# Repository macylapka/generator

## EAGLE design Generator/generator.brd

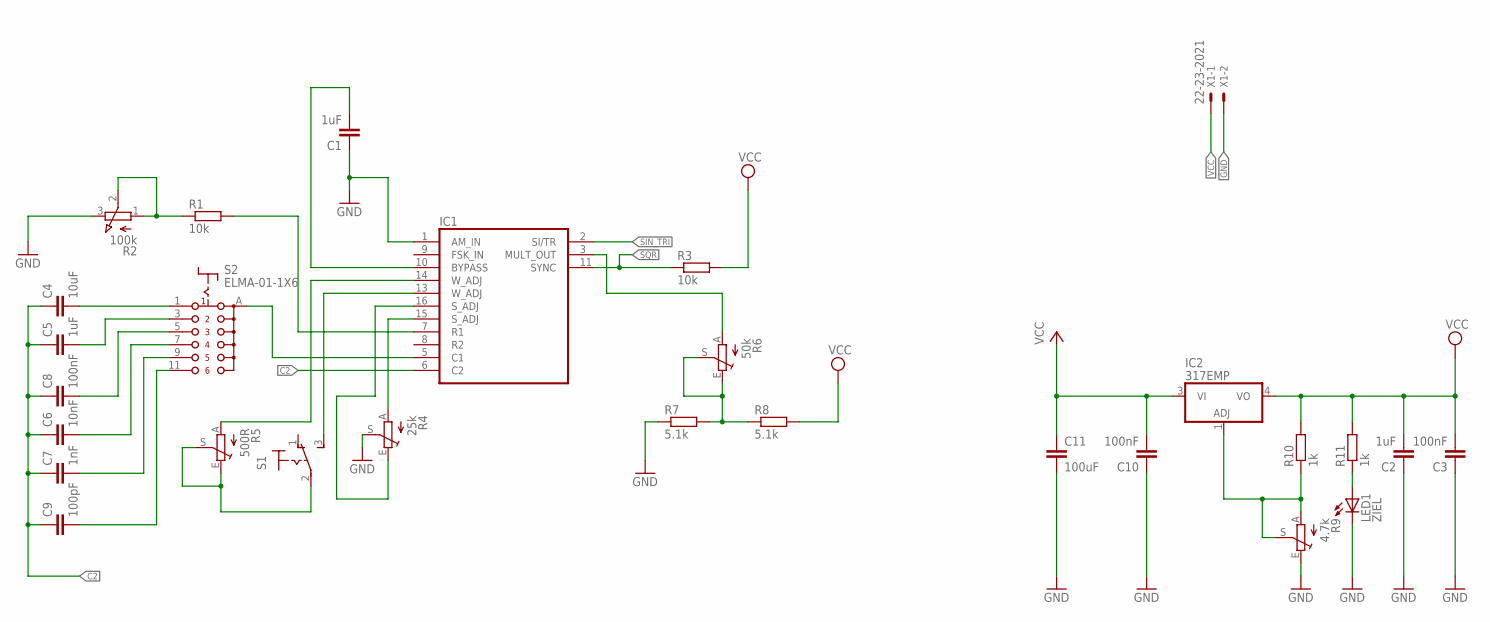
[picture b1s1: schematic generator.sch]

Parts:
C1, C2, C5: 1uF; C0805
C3, C8, C10: 100nF; C0805
C4: 10uF; C0805
C6: 10nF; C0805
C7: 1nF; C0805
C9: 100pF; C0805
C11: 100uF; C0805
IC1: XR-2206; DIL16
IC2: 317EMP; SOT223
LED1: ZIEL; LED_1206
R1, R3: 10k; R0805
R2: 100k; 3RP/1610N
R4: 25k; PT-SPIN
R5: 500R; PT-SPIN
R6: 50k; PT-SPIN
R7, R8: 5.1k; R0805
R9: 4.7k; PT-SPIN
R10, R11: 1k; R0805
S1: 320-916
S2: ELMA-01-1X6
X1: 22-23-2021

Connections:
C2: C4.1, C5.1, C6.1, C7.1, C8.1, C9.1, IC1.6 (C2)
GND: C1.1, C2.1, C3.1, C10.1, C11.2, IC1.1 (AM_IN), IC1.12 (GND), LED1.C, R2.3 (E), R4.S, R7.1, R9.E, X1.2
unnamed: C4.2, S2.1
unnamed: IC1.5 (C1), S2.A (S)
unnamed: C5.2, S2.3 (2)
unnamed: C8.2, S2.5 (3)
unnamed: C6.2, S2.7 (4)
unnamed: C7.2, S2.9 (5)
unnamed: IC1.7 (R1), R1.2
unnamed: C9.2, S2.11 (6)
unnamed: R1.1, R2.1 (A), R2.2 (S)
unnamed: C1.2, IC1.10 (BYPASS)
unnamed: R6.E, R6.S, R7.2, R8.1
unnamed: IC1.15 (S_ADJ), R4.A
unnamed: IC1.16 (S_ADJ), R4.E
unnamed: IC1.14 (W_ADJ), R5.A
unnamed: IC1.13 (W_ADJ), S1.3 (S)
unnamed: R5.E, R5.S, S1.2
unnamed: IC1.3 (MULT_OUT), R6.A
unnamed: LED1.A, R11.1
unnamed: IC2.1 (ADJ), R9.A, R9.S, R10.1
SIN_TRI: IC1.2 (SI/TR)
SQR: IC1.11 (SYNC), R3.1
VCC: C2.2, C3.2, C10.2, C11.1, IC1.4 (VCC), IC2.3 (VI), IC2.4 (VO), R3.2, R8.2, R10.2, R11.2, X1.1

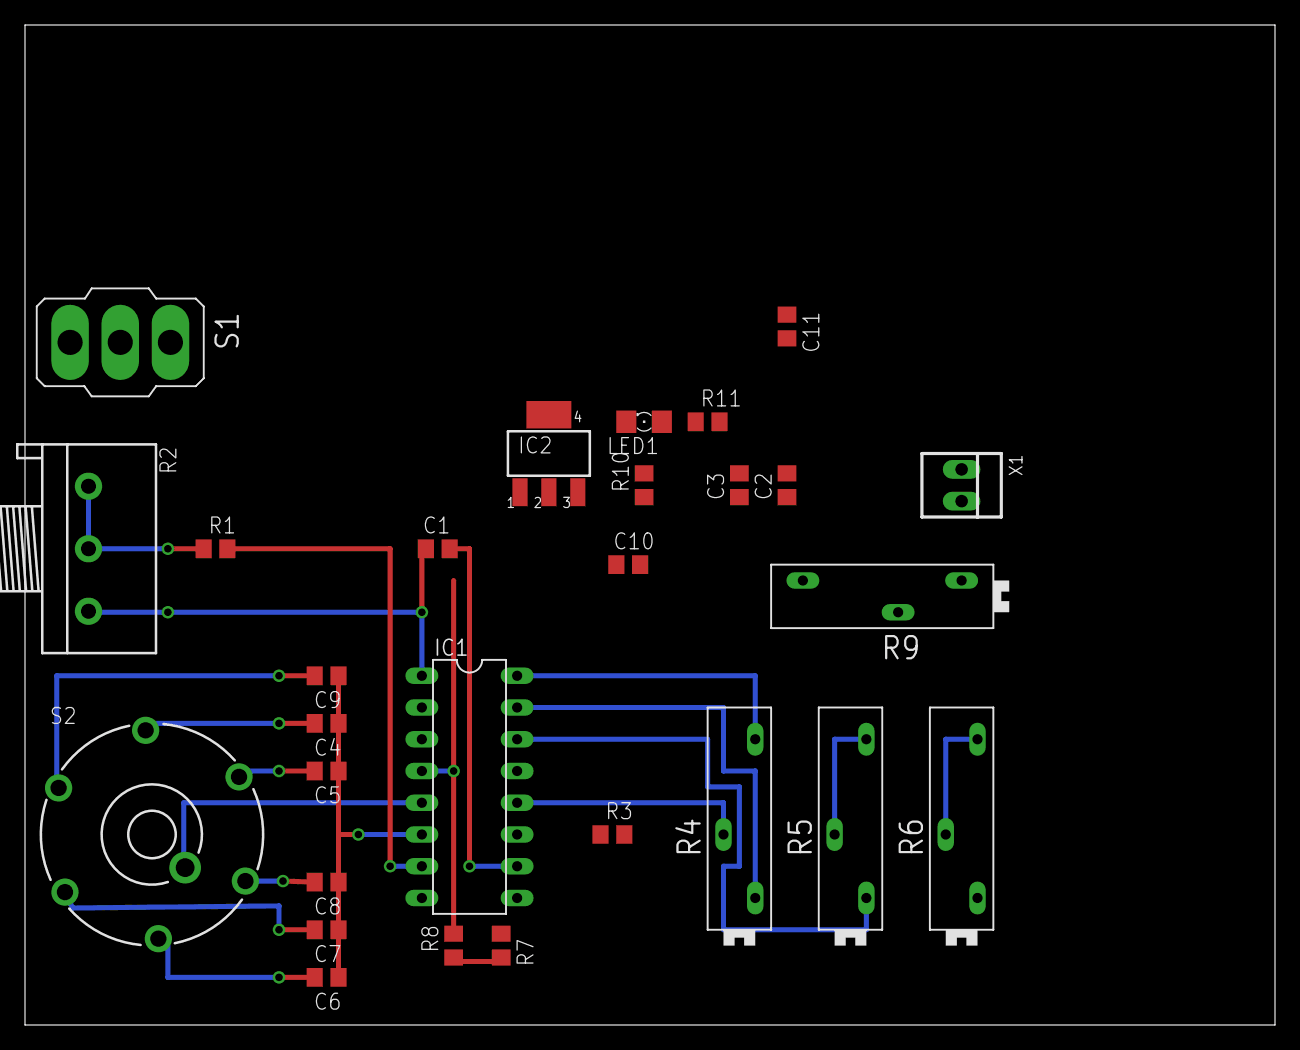
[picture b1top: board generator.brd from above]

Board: 2 copper layers, 100.0 x 80.0 mm, 28 parts (0 on the bottom side), 23 nets.

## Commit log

2015-06-21 test
2016-09-03 update board
2016-09-03 remove old folder
2016-09-03 more clean ups
